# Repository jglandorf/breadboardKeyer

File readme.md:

## Breadboard Keyer Demo for [ARROW](https://w8rp.org/) Field Day
### A Morse Code Practice Keyer Kit

### See the assembly documentation [here](doc/breadboardKeyer.odt).

#### Block diagram:

a) Power comes from an external USB power bank.  
b) This 5 volts powers the touch sensor-- it doesn’t directly power anything else!  
c) When the sensor is touched, its output turns on the tone generator.  
d) The tone generator output drives the mini speaker.  
Note:  a simplified variant may be built with an [active buzzer](https://www.aliexpress.us/item/3256809353431502.html) instead of the speaker; the '555' tone generator is then not used.

#### [Schematic](./breadboardKeyer.kicad_pro):  
There are four variations:
- micro USB breakout connector with passive speaker  
- USB C breakout connector with passive speaker  
- micro USB breakout connector with active buzzer
- USB C breakout connector with active buzzer

#### [Breadboard Layouts](./breadboardKeyer.kicad_pro):  
Passive buzzer/speaker with micro USB connector  

#### Passive buzzer/speaker with USB C connector  

#### Active buzzer with micro USB and USB C connectors  

### Bill-of-materials  
#### Summary for All Variants:  

| Reference | P/N |  Description | Link |  
| --- | --- | --- | ---- |  
| †qty ~3-5 | ??? | M-to-M breadboard jumper wires, 5-10cm | [AliExpress](https://www.aliexpress.us/item/3256809296261235.html) |  
| ‡qty 2 | ??? | M-to-M breadboard jumper ribbon, 5-10cm | [Amazon](https://www.amazon.com/dp/B01BV3Z342) |  
| qty 1 | ??? | 170-point mini breadboard | [Amazon](https://www.amazon.com/dp/B0DBDTBDS5?th=1) |  
| qty 1 | ??? | 3x3x3 inch craft paper box | [Amazon](https://www.amazon.com/dp/B0FXFWWB6K?th=1) |  
| qty 1 | 8376 |  ⃰ ⃰ Avery 2x3.5 card stock | e.g., [Amazon](https://www.amazon.com/Avery-Ink-Jet-Printer-Business-28371/dp/B00004Z5DG) |  
| qty ?? | ??? | ⃰heatshrink tubing as needed | [Amazon](https://www.amazon.com/dp/B0GGGY2HFJ) |  
| qty ?? | ??? | ⃰low-temp hot-glue sticks as needed | [Amazon](https://www.amazon.com/Surebonder-Low-Temp-Delicate-Materials-Balloons/dp/B003SBUAAI) |  
| J1, J3 | ??? | micro USB receptacle breakout | [Amazon](https://www.amazon.com/dp/B09XMQRNDL) |  
| J2, J4 | ??? | USB C receptacle breakout | [AliExpress](https://www.aliexpress.us/item/3256804610646385.html) |  
| BZ1, BZ2 | 5020 | 5x5x2mm speaker | [AliExpress](https://www.aliexpress.us/item/3256804070323228.html) |  
| BZ1, BZ2 | ??? | (alternate) PC speaker | [AliExpress](https://www.aliexpress.us/item/3256809886938359.html) |  
| BZ3, BZ4 | 9650 | 9.6x9.6x5mm 3V active buzzer | [AliExpress](https://www.aliexpress.us/item/3256809353431502.html) |  
| U2, U4, U5, U6 | TTP223 | TTP223 touch module | [AliExpress](https://www.aliexpress.us/item/2255800354323887.html) |  
| U1, U3 | NE555 | NE555 module | [AliExpress](https://www.aliexpress.us/item/3256806859546992.html) |  

† Jumper wires used for on-breadboard connections.
  Cut in half, these are soldered to the 5020 or 9650 speakers/buzzers  
‡ Ribbon jumper wires are plugged into the PC speakers/buzzers  
⃰ Use heatshrink to prevent separation of ribbon jumper wires, if needed.  Use hot glue to fill on top of speaker solder joints to prevent wire breakage.  
 ⃰ ⃰ Place card with github link to this page inside the kit's paper box.  Template is [here](doc/businessCards_bbkeyerKit_Avery8376.odt)

You will also need a USB power bank and appropriate USB cable-- not included in the kit.

#### Common to All Variants:  

| Quantity | P/N |  Description | Link |  
| --- | --- | --- | ---- |  
| †qty ~3-5 | ??? | M-to-M breadboard jumper wires, 5-10cm | [AliExpress](https://www.aliexpress.us/item/3256809296261235.html) |  
| ‡qty 2 | ??? | M-to-M breadboard jumper ribbon, 5-10cm | [Amazon](https://www.amazon.com/dp/B01BV3Z342) |  
| qty 1 | ??? | 170-point mini breadboard | [Amazon](https://www.amazon.com/dp/B0DBDTBDS5?th=1) |  
| qty 1 | ??? | 3x3x3 inch craft paper box | [Amazon](https://www.amazon.com/dp/B0FXFWWB6K?th=1) |  
| qty 1 of U2, U4, U5, or U6 | TTP223 | TTP223 touch module | [AliExpress](https://www.aliexpress.us/item/2255800354323887.html) |  

† Jumper wires used for on-breadboard connections.
  Cut in half, these are soldered to the 5020 or 9650 speakers/buzzers  
‡ Ribbon jumper wires are plugged into the PC speakers/buzzers  

#### Additional for Each Variant:
#### Micro USB breakout connector with passive speaker  

| Reference | P/N |  Description | Link |  
| --- | --- | --- | ---- |  
| J1 | ??? | micro USB receptacle breakout | [Amazon](https://www.amazon.com/dp/B09XMQRNDL) |  
| BZ1 | 5020 | 5x5x2mm speaker | [AliExpress](https://www.aliexpress.us/item/3256804070323228.html) |  
| BZ1 | ??? | (alternate) PC speaker | [AliExpress](https://www.aliexpress.us/item/3256809886938359.html) |  
| U1 | NE555 | NE555 module | [AliExpress](https://www.aliexpress.us/item/3256806859546992.html) |  

#### USB C breakout connector with passive speaker  

| Reference | P/N |  Description | Link |  
| --- | --- | --- | ---- |  
| J4 | ??? | USB C receptacle breakout | [AliExpress](https://www.aliexpress.us/item/3256804610646385.html) |  
| BZ2 | 5020 | 5x5x2mm speaker | [AliExpress](https://www.aliexpress.us/item/3256804070323228.html) |  
| BZ2 | ??? | (alternate) PC speaker | [AliExpress](https://www.aliexpress.us/item/3256809886938359.html) |  
| U3 | NE555 | NE555 module | [AliExpress](https://www.aliexpress.us/item/3256806859546992.html) |  

#### Micro USB breakout connector with active buzzer  

| Reference | P/N |  Description | Link |  
| --- | --- | --- | ---- |  
| J3 | ??? | micro USB receptacle breakout | [Amazon](https://www.amazon.com/dp/B09XMQRNDL) |  
| BZ3 | 9650 | 9.6x9.6x5mm 3V active buzzer | [AliExpress](https://www.aliexpress.us/item/3256809353431502.html) |  

#### USB C breakout connector with active buzzer  

| Reference | P/N |  Description | Link |  
| --- | --- | --- | ---- |  
| J4 | ??? | USB C receptacle breakout | [AliExpress](https://www.aliexpress.us/item/3256804610646385.html) |  
| BZ4 | 9650 | 9.6x9.6x5mm 3V active buzzer | [AliExpress](https://www.aliexpress.us/item/3256809353431502.html) |

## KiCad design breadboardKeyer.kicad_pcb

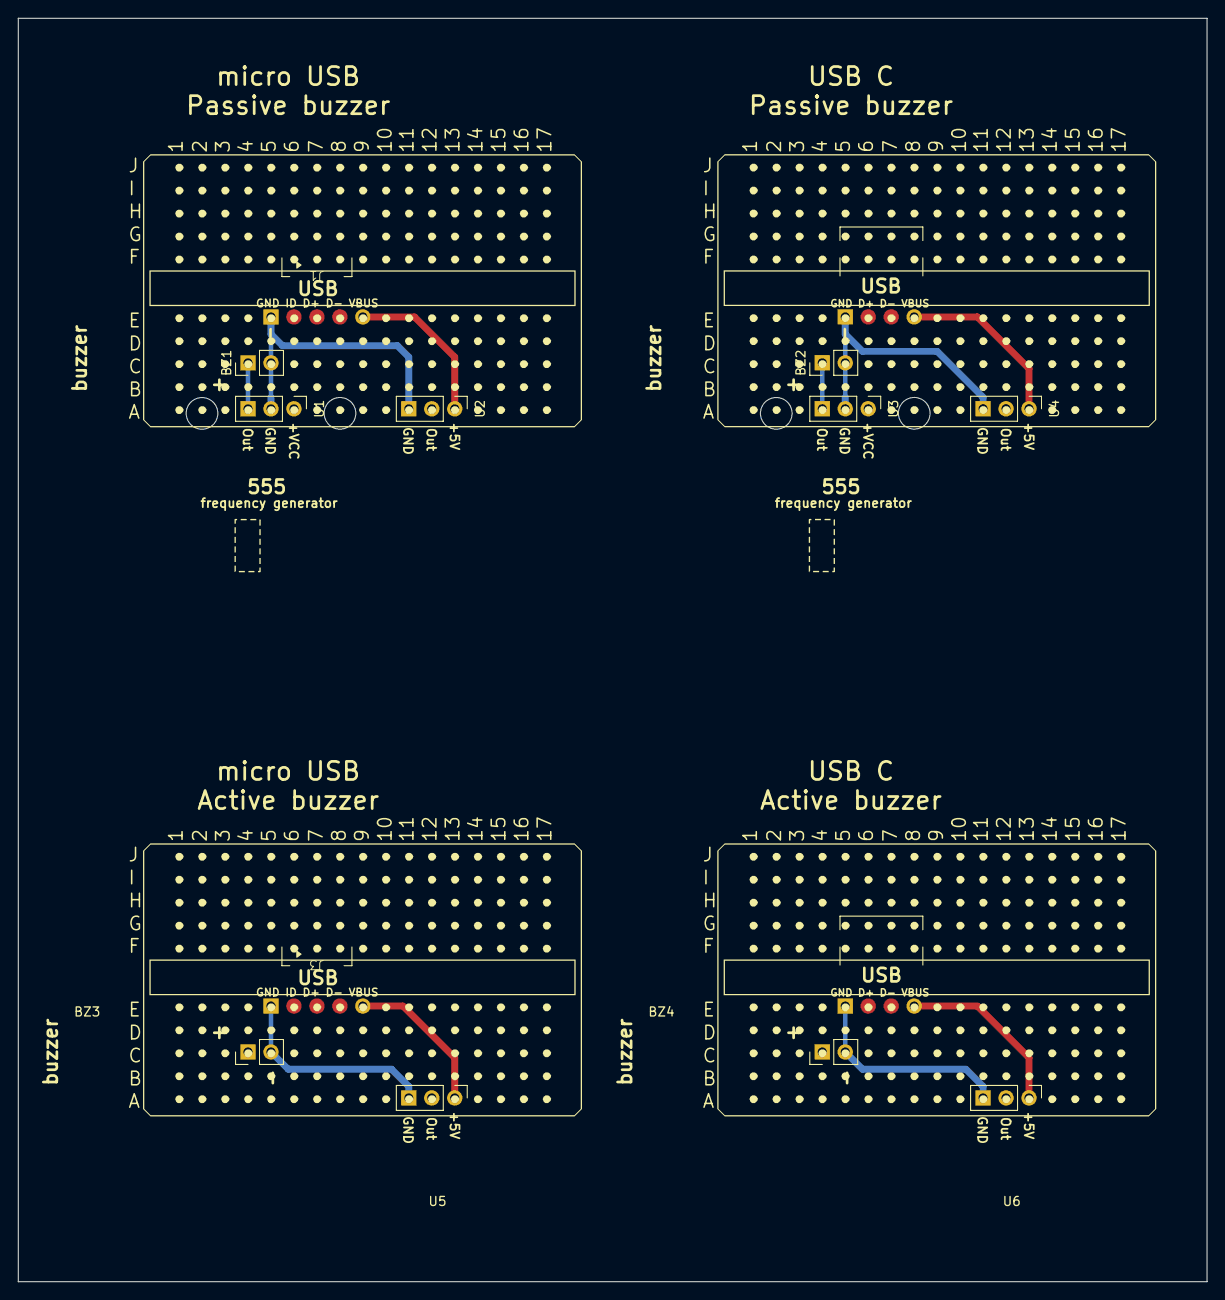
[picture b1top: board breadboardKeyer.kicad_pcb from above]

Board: 4 copper layers, 131.4 x 139.7 mm, 18 parts (0 on the bottom side), 14 nets.

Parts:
BZ1, BZ2: BuzzerPassive; Buzzer2020_Passive_1x02_P2.54mm_Horizontal
BZ3, BZ4: BuzzerActive; Buzzer5050_Active_1x02_P2.54mm_Horizontal
J1, J3: USB_micro; microUSBBreakout
J2: USB_C; cUSBBreakout
J4: USB_micro; cUSBBreakout
U1, U3: 555TimerModule; 555timerModule_1x03_P2.54mm_20z30mm
U2, U4, U5, U6: touchModule_TTP223; TTP223TouchModule_1x03_P2.54mm_10z14mm
Z1, Z2, Z3, Z4: LOGO; breadboard170_FSilkscreen

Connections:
/5V_cUSB: J2.4 (VBUS), U4.3 (Vcc)
/5V_cUSB2: J4.4 (VBUS), U6.3 (Vcc)
/5V_uUSB: J1.5 (VBUS), U2.3 (Vcc)
/5V_uUSB2: J3.5 (VBUS), U5.3 (Vcc)
/BuzOut1: BZ1.1 (+), U1.1 (Out)
/BuzOut2: BZ2.1 (+), U3.1 (Out)
/BuzOut3: BZ3.1 (+), U5.2 (I/O)
/BuzOut4: BZ4.1 (+), U6.2 (I/O)
/TouchOut1: U1.3 (Vcc), U2.2 (I/O)
/TouchOut2: U3.3 (Vcc), U4.2 (I/O)
GND1: BZ1.2 (-), J1.1 (GND), U1.2 (GND), U2.1 (GND)
GND2: BZ2.2 (-), J2.1 (GND), U3.2 (GND), U4.1 (GND)
GND3: BZ3.2 (-), J3.1 (GND), U5.1 (GND)
GND4: BZ4.2 (-), J4.1 (GND), U6.1 (GND)

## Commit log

2026-06-20 Initial commit. "Breadboard Keyer Demo for ARROW Field Day"
2026-06-20 Added BOM+costs in BOM/bom_cost.ods.
2026-06-24 Updated docs. Added sticker template for outside of box.
2026-06-25 Add assembly doc page numbers.
2026-06-26 Add quick checklist
2026-06-26 Add Morse code chart: https://upload.wikimedia.org/wikipedia/commons/b/b5/International_Morse_Code.svg
2026-06-26 Add 4-up Morse code chart; 1-up is from https://upload.wikimedia.org/wikipedia/commons/b/b5/International_Morse_Code.svg

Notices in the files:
breadboardKeyer.kicad_pcb:
(C) 2026 AC8ES
